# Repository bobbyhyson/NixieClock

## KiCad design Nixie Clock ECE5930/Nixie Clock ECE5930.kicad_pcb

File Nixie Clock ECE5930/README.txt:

Engineer: Bobby Thompson
Email: bobbythompson3333@gmail.com
Phone: +1 (801)-503-6088
Please contact about any issues! I appreciate it!! :)

EDA: KiCad 9

PCB
Conformal Coating: no
Green Soldermask
White Silscreen - Top, Bottom
Material FR4 TG135
Solder with Lead
Copper Weight: 1 oz

Gerber Format: RS-274-X2 Standard File Naming

Component Placement (imperial units):

Component BOM:

Notes:

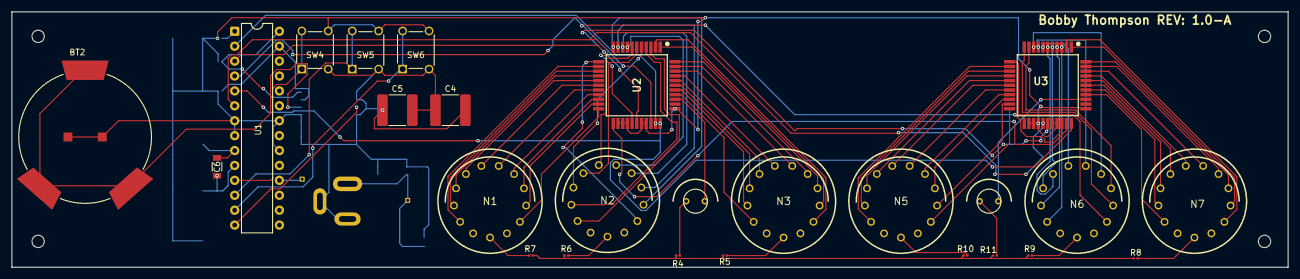
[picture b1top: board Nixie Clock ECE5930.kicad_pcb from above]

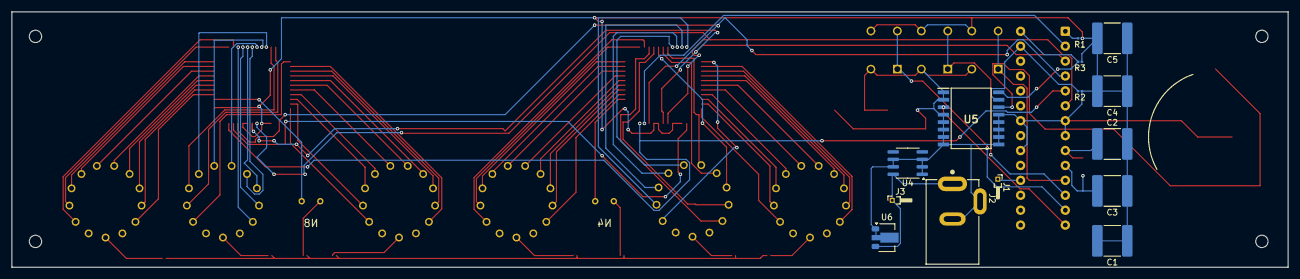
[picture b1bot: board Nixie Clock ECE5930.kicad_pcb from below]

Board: 2 copper layers, 217.4 x 43.5 mm, 40 parts (14 on the bottom side), 82 nets.

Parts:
BT2: BC-2600; BAT_BC-2600
C1, C4, C4#2, C5, C5#2: 0.1uF; C_2220_5750Metric
C2, C3: 22pF; C_2220_5750Metric
C6: ABS07-32.768KHZ-T; CAP_ABS07-32.768KHZ-T_ABR
J1: Conn_02x03_Top_Bottom; PinHeader_1x01_P1.00mm_Horizontal
J2: PJ-002B; CUI_PJ-002B
J3: Conn_01x03; PinHeader_1x01_P1.00mm_Horizontal
N1, N2, N3, N5, N6, N7: nixies-us-IN-14
N4, N8: IN-3; russian-nixies-IN-3
R1: 10K; R_0201_0603Metric
R2, R3: 7K; R_0201_0603Metric
R4, R11: 100K; R_0201_0603Metric
R5, R6, R7, R8, R9, R10: 27K; R_0201_0603Metric
SW4, SW5, SW6: 2-1825910-7; SW4_1825910-G_TEC
U1: ATmega328P-P; DIP-28_W7.62mm
U2, U3: HV5622; QFP80P1390X1390X235-44N
U4: L78L05_SO8; SOIC-8_3.9x4.9mm_P1.27mm
U5: DS3231N; SOIC127P1032X265-16N
U6: L78L05_SOT89; SOT-89-3

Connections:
+5V: BT2.1, BT2.2, C1.1, C1.2, C2.2, C3.1, C4.1, C4.2, C4#2.1, C4#2.2, C5.1, C5.2, C5#2.1, C5#2.2, J2.2, J2.3, R1.1, R2.1, R3.1, SW4.3, SW4.4, SW5.3, SW5.4, SW6.3, SW6.4, U1.7 (VCC), U1.8 (GND), U1.20 (AVCC), U1.22 (GND), U2.24 (N/C), U2.25 (N/C), U2.26 (N/C), U2.29 (VSS), U2.30 (VDD), U2.34 (N/C), U3.24 (N/C), U3.25 (N/C), U3.26 (N/C), U3.29 (VSS), U3.30 (VDD), U3.34 (N/C), U4.1 (OUT), U4.2 (GND), U4.3 (GND), U4.6 (GND), U4.7 (GND), U5.1 (32KHz), U5.2 (Vcc), U5.4 (!(Reset)), U5.5 (NC), U5.6 (NC), U5.7 (NC), U5.8 (NC), U5.9 (NC), U5.10 (NC), U5.11 (NC), U5.12 (NC), U5.13 (GND), U6.1 (OUT), U6.2 (GND)
+12V: J2.1, J3.1, U4.8 (IN), U6.3 (IN)
HT: R4.2, R5.2, R6.2, R7.2, R8.2, R9.2, R10.2, R11.1
unnamed: J1.1, U1.18 (PB4)
unnamed: R1.2, U1.1 (~RESET/PC6)
unnamed: U1.14 (PB0), U5.3 (!(INT)/SQR)
unnamed: R2.2, U1.27 (PC4), U5.15 (SDA)
unnamed: R3.2, U1.28 (PC5), U5.16 (SCL)
unnamed: U1.2 (PD0), U2.32 (DATAIN)
unnamed: U1.3 (PD1), U2.28 (CLK), U3.28 (CLK)
unnamed: U1.4 (PD2), U2.31 (~LE), U3.31 (~LE)
unnamed: U1.5 (PD3), U2.33 (~BL), U3.33 (~BL)
unnamed: U1.6 (PD4), U2.27 (~POL), U3.27 (~POL)
unnamed: SW4.1, SW4.2, U1.11 (PD5)
unnamed: SW5.1, SW5.2, U1.12 (PD6)
unnamed: SW6.1, SW6.2, U1.13 (PD7)
unnamed: C2.1, C6.2, U1.9 (XTAL1/PB6)
unnamed: C3.2, C6.1, U1.10 (XTAL2/PB7)
unnamed: U2.23 (DATAOUT), U3.32 (DATAIN)
unnamed: N1.1, U2.22 (HV1)
unnamed: N1.2, U2.21 (HV2)
unnamed: N1.3, U2.20 (HV3)
unnamed: N1.4, U2.19 (HV4)
unnamed: N1.5, U2.18 (HV5)
unnamed: N1.6, U2.17 (HV6)
unnamed: N1.7, U2.16 (HV7)
unnamed: N1.8, U2.15 (HV8)
unnamed: N1.9, U2.14 (HV9)
unnamed: N1.0, U2.13 (HV10)
unnamed: N2.1, U2.12 (HV11)
unnamed: N2.2, U2.11 (HV12)
unnamed: N2.3, U2.10 (HV13)
unnamed: N2.4, U2.9 (HV14)
unnamed: N2.5, U2.8 (HV15)
unnamed: N2.6, U2.7 (HV16)
unnamed: N2.7, U2.6 (HV17)
unnamed: N2.8, U2.5 (HV18)
unnamed: N2.9, U2.4 (HV19)
unnamed: N2.0, U2.3 (HV20)
unnamed: N3.1, U2.2 (HV21)
unnamed: N3.2, U2.1 (HV22)
unnamed: N3.3, U2.44 (HV23)
unnamed: N3.4, U2.43 (HV24)
unnamed: N3.5, U2.42 (HV25)
unnamed: N3.6, U2.41 (HV26)
unnamed: N3.7, U2.40 (HV27)
unnamed: N3.8, U2.39 (HV28)
unnamed: N3.9, U2.38 (HV29)
unnamed: N3.0, U2.37 (HV30)
unnamed: N4.K, U2.36 (HV31)
unnamed: N5.1, U3.22 (HV1)
unnamed: N5.2, U3.21 (HV2)
unnamed: N5.3, U3.20 (HV3)
unnamed: N5.4, U3.19 (HV4)
unnamed: N5.5, U3.18 (HV5)
unnamed: N5.6, U3.17 (HV6)
unnamed: N5.7, U3.16 (HV7)
unnamed: N5.8, U3.15 (HV8)
unnamed: N5.9, U3.14 (HV9)
unnamed: N5.0, U3.13 (HV10)
unnamed: N6.1, U3.12 (HV11)
unnamed: N6.2, U3.11 (HV12)
unnamed: N6.3, U3.10 (HV13)
unnamed: N6.4, U3.9 (HV14)
unnamed: N6.5, U3.8 (HV15)
unnamed: N6.6, U3.7 (HV16)
unnamed: N6.7, U3.6 (HV17)
unnamed: N6.8, U3.5 (HV18)
unnamed: N6.9, U3.4 (HV19)
unnamed: N6.0, U3.3 (HV20)
unnamed: N7.1, U3.2 (HV21)
unnamed: N7.2, U3.1 (HV22)
unnamed: N7.3, U3.44 (HV23)
unnamed: N7.4, U3.43 (HV24)
unnamed: N7.5, U3.42 (HV25)
unnamed: N7.6, U3.41 (HV26)
unnamed: N7.7, U3.40 (HV27)
unnamed: N7.8, U3.39 (HV28)
unnamed: N7.9, U3.38 (HV29)
unnamed: N7.0, U3.37 (HV30)
unnamed: N8.K, U3.36 (HV31)
unnamed: BT2.S1, BT2.S2, BT2.S3, U5.14 (Vbat)

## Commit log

2025-11-06 moving shit around i think
2025-11-10 rewire
2025-11-10 added button STEP
2025-11-13 holy shit im gonna die
2025-11-13 3d models yum
2025-11-13 final commit i hope
2025-11-13 final revision before submission
2025-11-17 final build maybe?
